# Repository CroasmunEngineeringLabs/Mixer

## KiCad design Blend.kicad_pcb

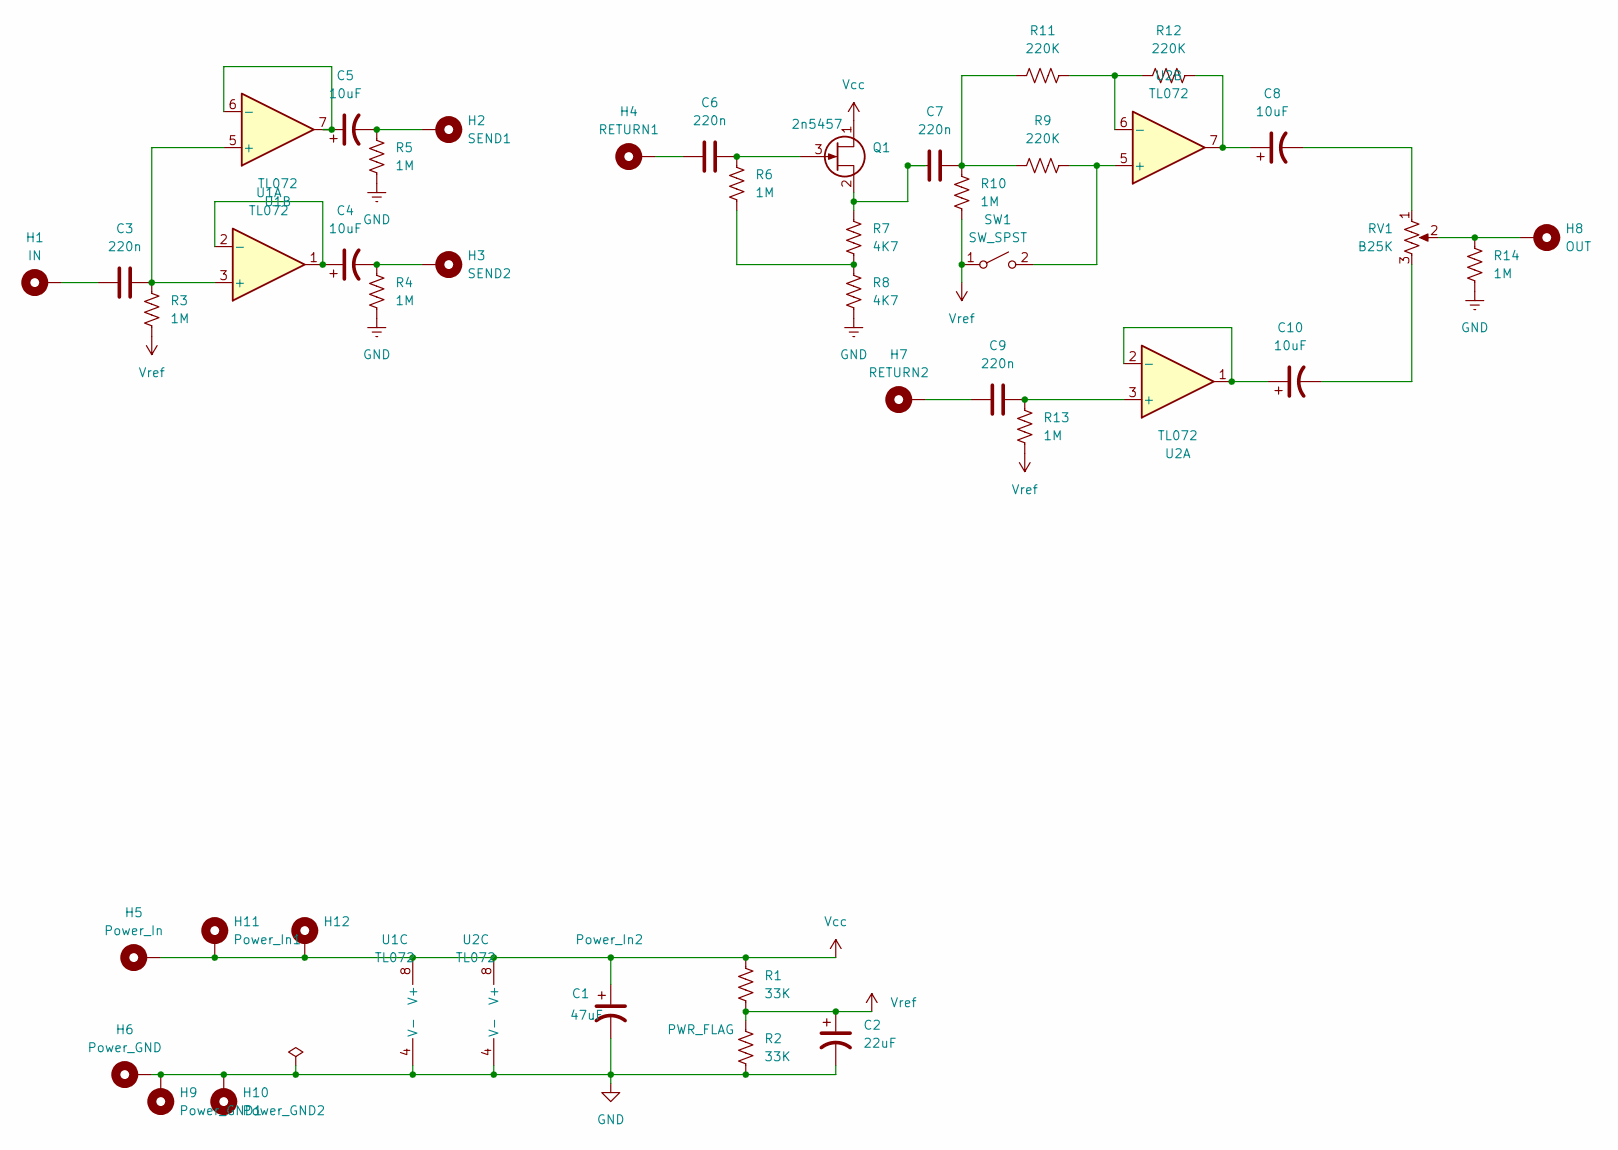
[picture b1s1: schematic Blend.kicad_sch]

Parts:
C1: 47uF; CAP_ELEC_10UF_35V
C2: 22uF; CAP_ELEC_10UF_35V
C3, C6, C7, C9: 220n; CAP_FILM_100NF
C4, C5, C8, C10: 10uF; CAP_ELEC_33UF_35V
H1: IN; PAD_2MM
H2: SEND1; PAD_2MM
H3: SEND2; PAD_2MM
H4: RETURN1; PAD_2MM
H5: Power_In; PAD_2MM
H6: Power_GND; PAD_2MM
H7: RETURN2; PAD_2MM
H8: OUT; PAD_2MM
H9: Power_GND1; PAD_2MM
H10: Power_GND2; PAD_2MM
H11: Power_In1; PAD_2MM
H12: Power_In2; PAD_2MM
Q1: 2n5457; BJT_2N5458
R1, R2: 33K; R_Axial_DIN0207_L6.3mm_D2.5mm_P7.62mm_Horizontal
R3, R4, R5, R6, R10, R13, R14: 1M; R_Axial_DIN0207_L6.3mm_D2.5mm_P7.62mm_Horizontal
R7, R8: 4K7; R_Axial_DIN0207_L6.3mm_D2.5mm_P7.62mm_Horizontal
R9, R11, R12: 220K; R_Axial_DIN0207_L6.3mm_D2.5mm_P7.62mm_Horizontal
RV1: B25K; POT_16MM_RA
SW1: SW_SPST; SW_DIP_SPSTx01_Slide_6.7x4.1mm_W7.62mm_P2.54mm_LowProfile
U1, U2: TL072; OP_AMP

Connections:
GND: C1.2, C2.2, H6.1, H9.1, H10.1, R2.2, R4.2, R5.2, R8.2, R14.2, U1.4 (V-), U2.4 (V-)
unnamed: C3.1, H1.1
unnamed: C4.2, H3.1, R4.1
unnamed: C5.2, H2.1, R5.1
unnamed: C6.1, H4.1
unnamed: C7.2, R9.1, R10.1, R11.1
unnamed: C8.1, R12.2, U2.7
unnamed: C8.2, RV1.1
unnamed: C9.1, H7.1
unnamed: C10.2, RV1.3
unnamed: H8.1, R14.1, RV1.2
unnamed: C6.2, Q1.3 (G), R6.1
unnamed: C7.1, Q1.2 (S), R7.1
unnamed: R6.2, R7.2, R8.1
unnamed: R9.2, SW1.2 (B), U2.5 (+)
unnamed: C3.2, R3.1, U1.3 (+), U1.5 (+)
unnamed: C4.1, U1.1, U1.2 (-)
unnamed: C5.1, U1.6 (-), U1.7
unnamed: C9.2, R13.1, U2.3 (+)
unnamed: C10.1, U2.1, U2.2 (-)
unnamed: R11.2, R12.1, U2.6 (-)
Vcc: C1.1, H5.1, H11.1, H12.1, Q1.1 (D), R1.1, U1.8 (V+), U2.8 (V+)
Vref: C2.1, R1.2, R2.1, R3.2, R10.2, R13.2, SW1.1 (A)

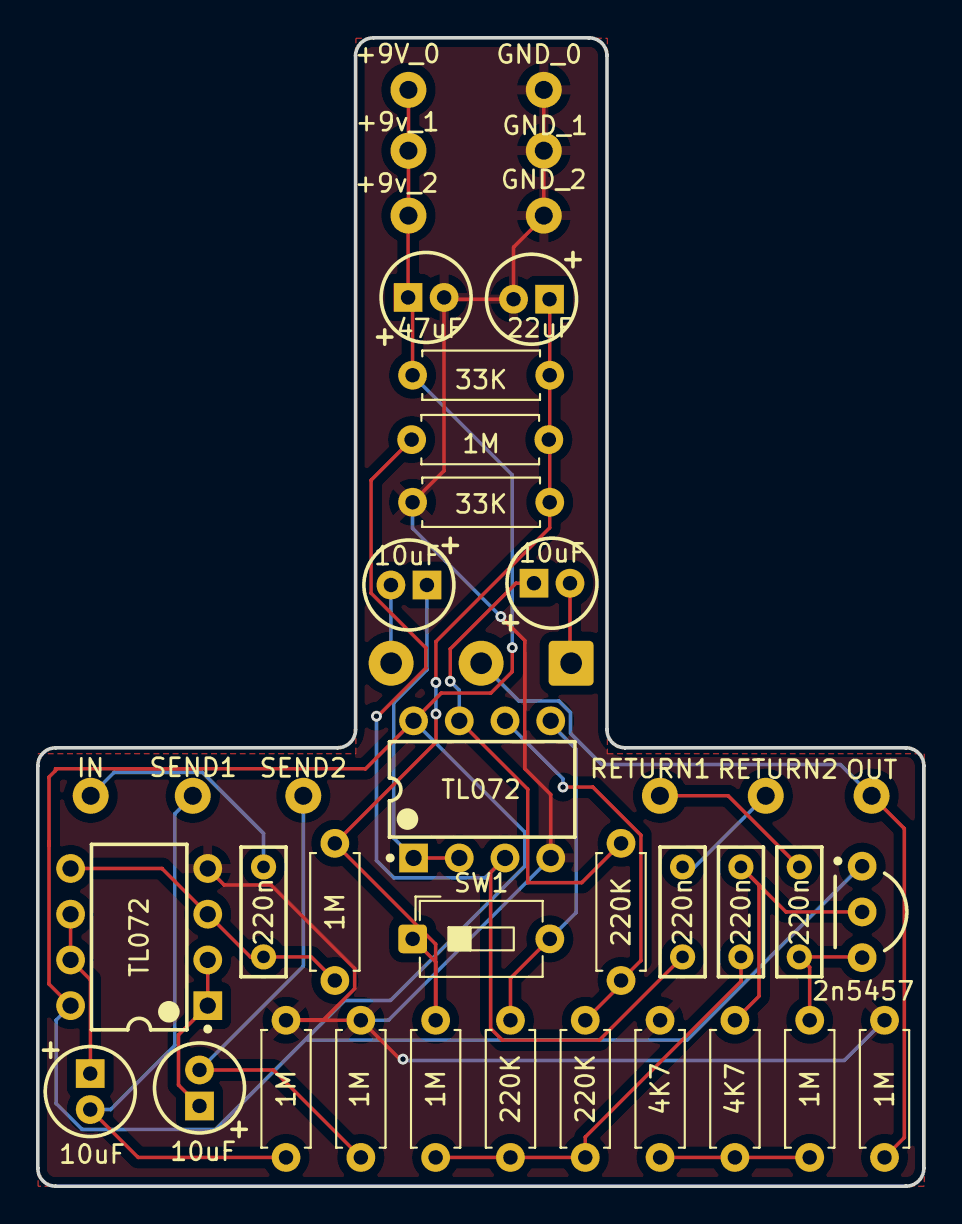
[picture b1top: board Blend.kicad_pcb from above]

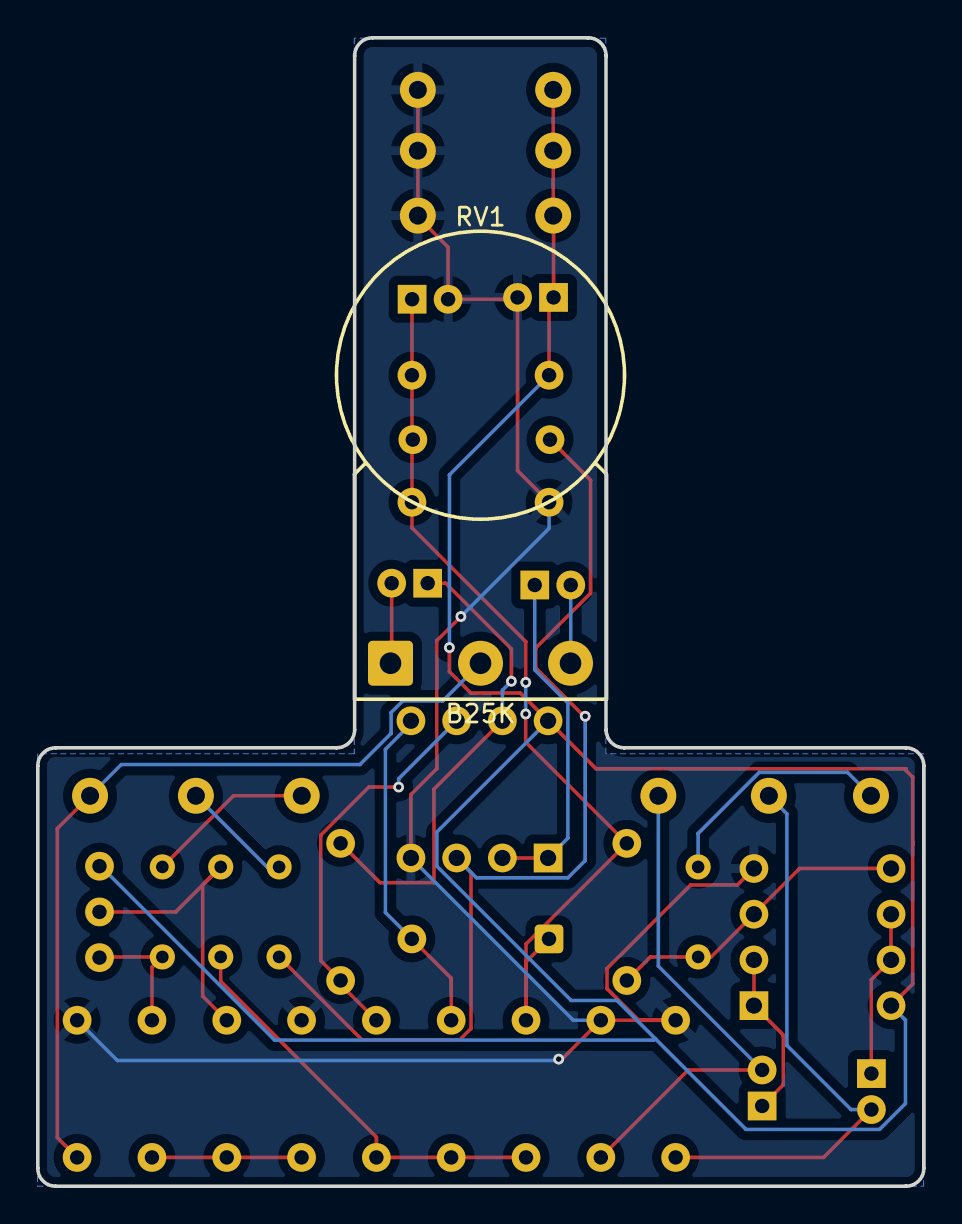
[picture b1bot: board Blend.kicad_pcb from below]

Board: 2 copper layers, 49.2 x 63.8 mm, 41 parts (2 on the bottom side), 23 nets.
